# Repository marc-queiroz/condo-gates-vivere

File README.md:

# condo-gates-vivere

# Working version
Python 3.6.4 (default, Jan 25 2018, 15:20:29) 
[GCC 7.2.1 20180116] on linux

## Running on raspberry pi rev0010

## How to run

python -m venv .

pip install -r requirements

python relay.py

## Project includes

Arduinos source code for gates simulator

Schematics for connections between **Raspberry Pi** and **Arduino**.

Observation: The Solid state relay should be replaced by a 5V relay with 3 pins VCC, GROUND and IN.

# Project on circuit-diagram.org

https://crcit.net/c/c7c45868cee941868d9534cdedbfd286

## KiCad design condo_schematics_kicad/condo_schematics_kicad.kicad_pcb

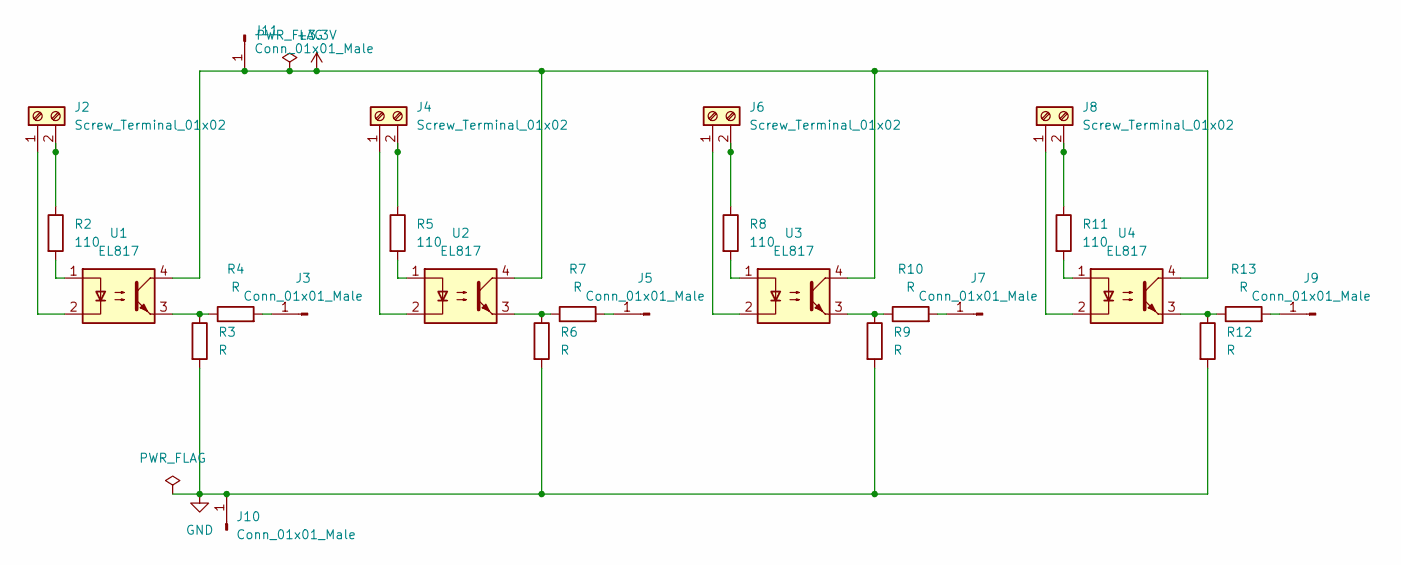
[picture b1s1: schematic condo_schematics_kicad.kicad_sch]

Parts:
J2, J4, J6, J8: Screw_Terminal_01x02; TerminalBlock_Altech_AK300-2_P5.00mm
J3, J5, J7, J9, J10, J11: Conn_01x01_Male; PinHeader_1x01_P2.54mm_Vertical
R2, R5, R8, R11: 110; R_Axial_DIN0207_L6.3mm_D2.5mm_P7.62mm_Horizontal
R3, R4, R6, R7, R9, R10, R12, R13: R; R_Axial_DIN0207_L6.3mm_D2.5mm_P7.62mm_Horizontal
U1, U2, U3, U4: EL817; DIP-4_W7.62mm

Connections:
+3V3: J11.1, U1.4, U2.4, U3.4, U4.4
GND: J10.1, R3.2, R6.2, R9.2, R12.2
unnamed: J2.1, U1.2
unnamed: J2.2, R2.1
unnamed: J3.1, R4.2
unnamed: J4.1, U2.2
unnamed: J4.2, R5.1
unnamed: J5.1, R7.2
unnamed: J6.1, U3.2
unnamed: J6.2, R8.1
unnamed: J7.1, R10.2
unnamed: J8.1, U4.2
unnamed: J8.2, R11.1
unnamed: J9.1, R13.2
unnamed: R2.2, U1.1
unnamed: R3.1, R4.1, U1.3
unnamed: R5.2, U2.1
unnamed: R6.1, R7.1, U2.3
unnamed: R8.2, U3.1
unnamed: R9.1, R10.1, U3.3
unnamed: R11.2, U4.1
unnamed: R12.1, R13.1, U4.3

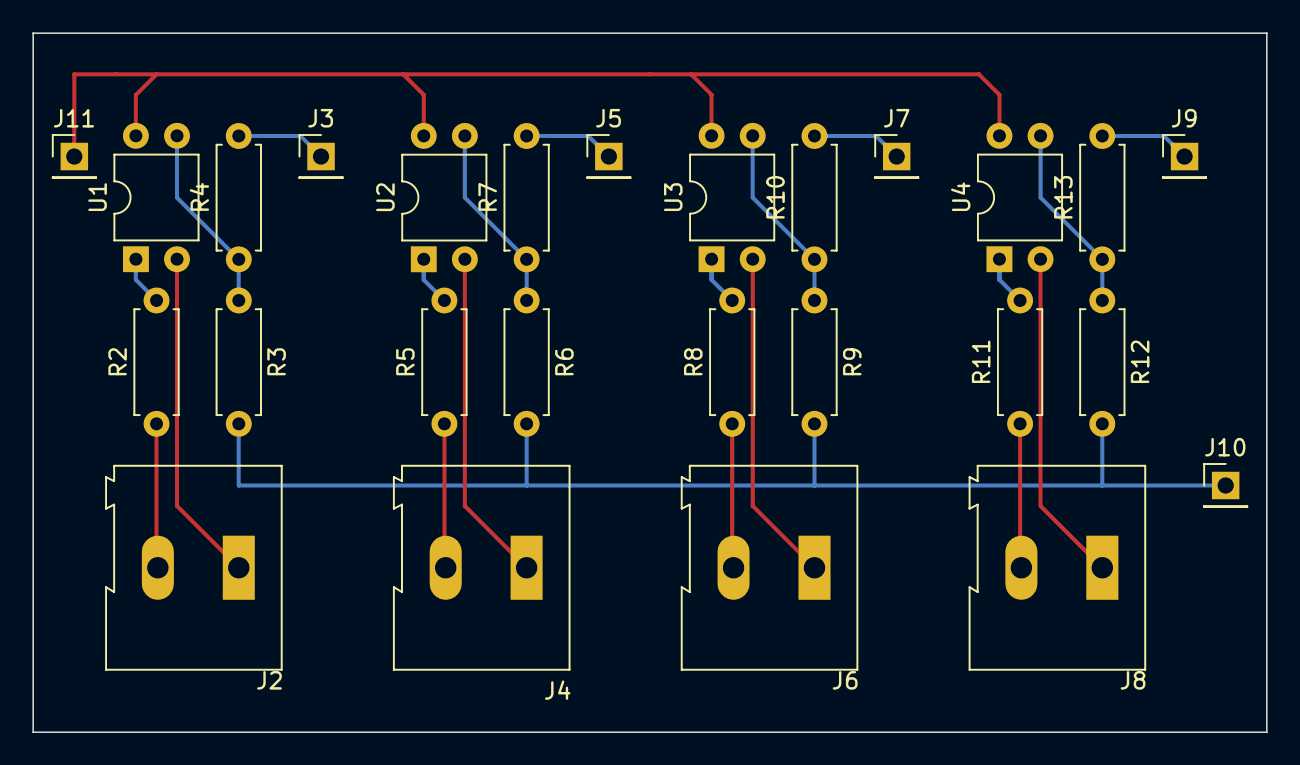
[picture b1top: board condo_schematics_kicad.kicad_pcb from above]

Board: 2 copper layers, 76.2 x 43.2 mm, 26 parts (0 on the bottom side), 22 nets.

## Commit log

2022-04-04 Programming for raspberry PI to run two gates doors simultaneously
    - Radio input for 2 gates
    - Sensor for gates operation
    - Relay to action the gates
2022-04-04 Adding arduino mega 2560 - Gates simulator
    - Without a real gate input and output, this code was created to
    simulate to independent gates. The purpose of the all project is to
    prevent the activation of both gates, cause of accidents in the
    condominium.
2022-04-04 Instructions for the project
    - Schematics for connects between Arduino and Raspberry Pi
2022-04-04 Adding URL to Circuit Diagram project
2022-04-04 Adding schematics
    CDDX file for circuit-diagram.org.
    Netlist, compatible with program SPICE see wikepedia.
    PNG and SVG circuit representation.
2022-04-17 Adding mutex to the code and changing the gpio pin
2022-04-17 Adding systemd scripts to repository
2022-04-22 Adding a initial circuit with schematics and pcb working
2022-04-24 Adding kicad schematics and PCB
2022-04-24 Adding gitignore
2022-04-24 Cleaning test schematics and PCBs
2022-04-25 Adding new rules to avoid colision between the gates
    - If both gates are detected in same time, none will activate the gates.
2022-05-07 Fixing relay getting fired by neighboard pins
    - When a relay is fired the oder relay should not be ON.
    - In case of trying to fire the gate detect the other relay active should return
2022-05-10 Changing relay pins to avoid electrical noise
